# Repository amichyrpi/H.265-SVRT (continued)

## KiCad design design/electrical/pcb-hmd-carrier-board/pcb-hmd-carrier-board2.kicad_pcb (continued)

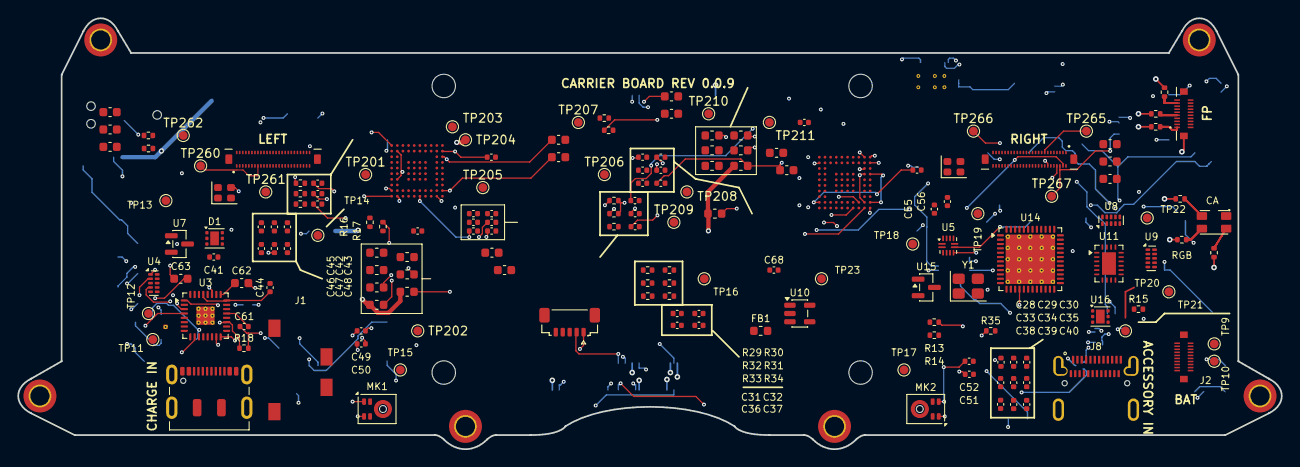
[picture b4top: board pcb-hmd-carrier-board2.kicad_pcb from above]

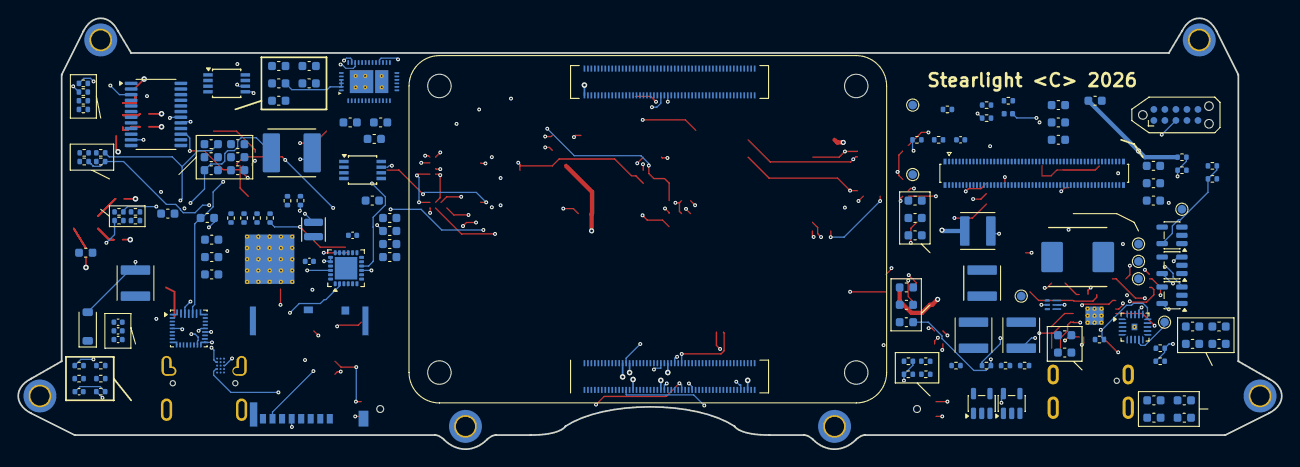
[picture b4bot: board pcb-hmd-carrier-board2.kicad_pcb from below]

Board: 6 copper layers, 145.5 x 49.6 mm, 312 parts (138 on the bottom side), 277 nets.

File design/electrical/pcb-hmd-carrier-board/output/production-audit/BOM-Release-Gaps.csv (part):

Reference,Value,Missing_release_fields
C1,10u,Manufacturer; MPN; Supplier part number
C10,10u,Manufacturer; MPN; Supplier part number
C11,10u,Manufacturer; MPN; Supplier part number
C12,100n,Manufacturer; MPN; Supplier part number
C13,10u,Manufacturer; MPN; Supplier part number
C14,10u,Manufacturer; MPN; Supplier part number
C15,100n,Manufacturer; MPN; Supplier part number
C16,4u7,Manufacturer; MPN; Supplier part number
C17,47n,Manufacturer; MPN; Supplier part number
C18,47n,Manufacturer; MPN; Supplier part number
C19,10u,Manufacturer; MPN; Supplier part number
C2,10u,Manufacturer; MPN; Supplier part number
C20,10u,Manufacturer; MPN; Supplier part number
C2010,100n,Manufacturer; MPN; Supplier part number
C2011,100n,Manufacturer; MPN; Supplier part number
C2012,100n,Manufacturer; MPN; Supplier part number
C20120,1u,Manufacturer; MPN; Supplier part number
C20121,1u,Manufacturer; MPN; Supplier part number
C20122,2.2u,Manufacturer; MPN; Supplier part number
C20123,2.2u,Manufacturer; MPN; Supplier part number
C2013,100n,Manufacturer; MPN; Supplier part number
C20130,100n,Manufacturer; MPN; Supplier part number
C20131,100n,Manufacturer; MPN; Supplier part number
C20132,100n,Manufacturer; MPN; Supplier part number
C2014,100n,Manufacturer; MPN; Supplier part number
C2015,100n,Manufacturer; MPN; Supplier part number
C2016,100n,Manufacturer; MPN; Supplier part number
C2017,100n,Manufacturer; MPN; Supplier part number
C2020,100n,Manufacturer; MPN; Supplier part number
C2021,100n,Manufacturer; MPN; Supplier part number
C2022,100n,Manufacturer; MPN; Supplier part number
C20220,1u,Manufacturer; MPN; Supplier part number
C20221,1u,Manufacturer; MPN; Supplier part number
C20222,2.2u,Manufacturer; MPN; Supplier part number
C20223,2.2u,Manufacturer; MPN; Supplier part number
C2023,100n,Manufacturer; MPN; Supplier part number
C20230,100n,Manufacturer; MPN; Supplier part number
C20231,100n,Manufacturer; MPN; Supplier part number
C20232,100n,Manufacturer; MPN; Supplier part number
C2024,100n,Manufacturer; MPN; Supplier part number
C2025,100n,Manufacturer; MPN; Supplier part number
C2026,100n,Manufacturer; MPN; Supplier part number
C2027,100n,Manufacturer; MPN; Supplier part number
C2031,4.7uF 10V,Manufacturer; MPN; Supplier part number
C2032,10uF 6.3V,Manufacturer; MPN; Supplier part number
C2041,4.7uF 10V,Manufacturer; MPN; Supplier part number
C2042,10uF 6.3V,Manufacturer; MPN; Supplier part number
C2051,4.7uF 10V,Manufacturer; MPN; Supplier part number
C2052,10uF 6.3V,Manufacturer; MPN; Supplier part number
C2061,4.7uF 10V,Manufacturer; MPN; Supplier part number
C2062,10uF 6.3V,Manufacturer; MPN; Supplier part number
C21,10u,Manufacturer; MPN; Supplier part number
C22,10u,Manufacturer; MPN; Supplier part number
C23,10u,Manufacturer; MPN; Supplier part number
C24,100n,Manufacturer; MPN; Supplier part number
C25,100n,Manufacturer; MPN; Supplier part number
C26,1u,Manufacturer; MPN; Supplier part number
C260,2.2uF,Manufacturer; MPN; Supplier part number
C261,1uF 10V,Manufacturer; MPN; Supplier part number
C262,1uF 10V,Manufacturer; MPN; Supplier part number
C265,2.2uF,Manufacturer; MPN; Supplier part number
C266,1uF 10V,Manufacturer; MPN; Supplier part number
C267,1uF 10V,Manufacturer; MPN; Supplier part number
C27,47p,Manufacturer; MPN; Supplier part number
C270,4.7uF 10V,Manufacturer; MPN; Supplier part number
C271,2.2uF 10V,Manufacturer; MPN; Supplier part number
C272,4.7uF 10V,Manufacturer; MPN; Supplier part number
C273,4.7uF 10V,Manufacturer; MPN; Supplier part number
C274,1uF,Manufacturer; MPN; Supplier part number
C28,100n,Manufacturer; MPN; Supplier part number
C280,68n COMP,Manufacturer; MPN; Supplier part number
C281,10uF 10V,Manufacturer; MPN; Supplier part number
C282,10uF 16V,Manufacturer; MPN; Supplier part number
C283,10uF 16V,Manufacturer; MPN; Supplier part number
C29,100n,Manufacturer; MPN; Supplier part number
C290,100n,Manufacturer; MPN; Supplier part number
C291,100n,Manufacturer; MPN; Supplier part number
C3,10u,Manufacturer; MPN; Supplier part number
C30,100n,Manufacturer; MPN; Supplier part number
C301,10uF SD POWER (CM4 LITE ONLY),Manufacturer; MPN; Supplier part number
C31,100n,Manufacturer; MPN; Supplier part number
C32,100n,Manufacturer; MPN; Supplier part number
C33,100n,Manufacturer; MPN; Supplier part number
C34,100n,Manufacturer; MPN; Supplier part number
C35,100n,Manufacturer; MPN; Supplier part number
C36,100n,Manufacturer; MPN; Supplier part number
C37,100n,Manufacturer; MPN; Supplier part number
C38,10u,Manufacturer; MPN; Supplier part number
C39,1u,Manufacturer; MPN; Supplier part number
C4,10u,Manufacturer; MPN; Supplier part number
C40,1u,Manufacturer; MPN; Supplier part number
C41,1u,Manufacturer; MPN; Supplier part number
C42,1u,Manufacturer; MPN; Supplier part number
C43,100n,Manufacturer; MPN; Supplier part number
C44,10u,Manufacturer; MPN; Supplier part number
C45,10u,Manufacturer; MPN; Supplier part number
C46,10u,Manufacturer; MPN; Supplier part number
C47,10u,Manufacturer; MPN; Supplier part number
C48,100n,Manufacturer; MPN; Supplier part number
C49,1u C0G,Manufacturer; MPN; Supplier part number
C5,10u,Manufacturer; MPN; Supplier part number
C50,1u C0G,Manufacturer; MPN; Supplier part number
C51,1u C0G,Manufacturer; MPN; Supplier part number
C52,1u C0G,Manufacturer; MPN; Supplier part number
C55,100n PCIe AC,Manufacturer; MPN; Supplier part number
C56,100n PCIe AC,Manufacturer; MPN; Supplier part number
C57,100u low-ESR,Manufacturer; MPN; Supplier part number
C58,100u low-ESR,Manufacturer; MPN; Supplier part number
C59,22u 25V,Manufacturer; MPN; Supplier part number
C6,100n,Manufacturer; MPN; Supplier part number
C60,22u 25V,Manufacturer; MPN; Supplier part number
C61,100n JACK MIC,Manufacturer; MPN; Supplier part number
C62,47u HP LEFT,Manufacturer; MPN; Supplier part number
C63,47u HP RIGHT,Manufacturer; MPN; Supplier part number
C64,4.7u 10V,Manufacturer; MPN; Supplier part number
C65,10u 6.3V,Manufacturer; MPN; Supplier part number
C66,10u 6.3V,Manufacturer; MPN; Supplier part number
C67,120p C0G,Manufacturer; MPN; Supplier part number
C68,100n USB3 RESET,Manufacturer; MPN; Supplier part number
C7,330p,Manufacturer; MPN; Supplier part number
C8,330p,Manufacturer; MPN; Supplier part number
C9,10u,Manufacturer; MPN; Supplier part number
D1,TVS2200DRVR,Manufacturer; MPN; Supplier part number
D11,TJ-S3227 RGB COMMON ANODE C601674,Manufacturer; MPN; Supplier part number
D201,DFLS160-7,Manufacturer; MPN; Supplier part number
FB1,600R@100MHz ferrite,Manufacturer; MPN; Supplier part number
FB2011,600R@100MHz,Manufacturer; MPN; Supplier part number
FB2012,600R@100MHz,Manufacturer; MPN; Supplier part number
FB2013,600R@100MHz,Manufacturer; MPN; Supplier part number
FB2014,600R@100MHz,Manufacturer; MPN; Supplier part number
FB2015,600R@100MHz,Manufacturer; MPN; Supplier part number
FB2016,600R@100MHz,Manufacturer; MPN; Supplier part number
FB2017,600R@100MHz,Manufacturer; MPN; Supplier part number
FB2021,600R@100MHz,Manufacturer; MPN; Supplier part number
FB2022,600R@100MHz,Manufacturer; MPN; Supplier part number
FB2023,600R@100MHz,Manufacturer; MPN; Supplier part number
FB2024,600R@100MHz,Manufacturer; MPN; Supplier part number
FB2025,600R@100MHz,Manufacturer; MPN; Supplier part number
FB2026,600R@100MHz,Manufacturer; MPN; Supplier part number
FB2027,600R@100MHz,Manufacturer; MPN; Supplier part number
J1,SJ-43514-SMT-TR,Manufacturer; MPN; Supplier part number
J10,PROX SENSOR - SM05B-SURS-TF,Manufacturer; MPN; Supplier part number
J11,BM28B0.6-20DS/2-0.35V BUTTON FLEX,Manufacturer; MPN; Supplier part number
J2,BM28 BATTERY FLEX 5A + NTC/ID,Manufacturer; MPN; Supplier part number
J201,J_DISPLAY_LEFT 245863050104829+,Manufacturer; MPN; Supplier part number
J202,J_DISPLAY_RIGHT 245863050104829+,Manufacturer; MPN; Supplier part number
J301,Molex 503398-1892 (CM4 LITE ONLY),Manufacturer; MPN; Supplier part number
J7,DF40C-100DP-0.4V(51) TRACKING,Manufacturer; MPN; Supplier part number
J8,DX07S024JJ2R1300 ACCESSORY,Manufacturer; MPN
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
